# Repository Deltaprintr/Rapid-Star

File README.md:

# Overview

Rapid Star is a PNP (Pick and Place) system developed and maintained by [Deltaprintr](https://deltaprintr.com), run on the free [OpenPNP Software](https://openpnp.org) and [Mark's Smoothieware Firmware Version](https://makr.zone/smoothieware-new-firmware-for-pnp/500/) used for assembling circuit boards with the [Rapid Feeder](https://www.deltaprintr.com/product/rapid-feeder/) system. It features a conveyor belt that can hold boards up to 165mm (6.5") wide, 50 (8mm) feeders and has a head capable of supporting up to 8 nozzles with a 20 nozzle magazine auto-changer. Documentation on building a Rapid Star can be found [on our website](https://www.deltaprintr.com/docs/rapid-star/). The release is considered stable as the machine has been fully tested manually. If you would like to show your support for the project, consider purchasing [components directly from Deltaprintr](https://www.deltaprintr.com/product-category/smt-assembly/). This not only allows us to continue developing the Rapid Star, but also enables us to provide support directly to you in the process.

If you'd like to find out once Deltaprintr starts offering a complete kit, you can subscribe to our [mailing list](https://mailchi.mp/ee676e0cfc9f/rapidstar)

# Benefits of a star design
- Scalable nozzle count at no additional cost
- Higher CPH
- Simpler mechanical assembly
- More X/Y space due to smaller head, which means more space for feeders/trays.

# Contribute

Currently the Rapid Star is not fully supported in OpenPNP due to a few missing mandatory features. We're actively looking for developers who would be interested in helping us incorporate support into OpenPNP. You can see the [full list of features here](https://docs.google.com/document/d/1N6ggEopUlor0r7kC39QZDpr8pi3T8QCvNgg1l5aPtP0/edit?usp=sharing). If you're interested in helping, let us know on our [Discord Server](https://discord.gg/t2FcjAU7hC)!

If you'd like to keep up with the latest news you can also follow us on [Instagram](https://www.instagram.com/deltaprintr/), [Facebook](https://www.facebook.com/Deltaprintr/) or [Twitter](https://twitter.com/deltaprintr)!

# Support

While you are free to source and build a Rapid Star on your own, we are only able to provide support for customers who purchase components directly from us. This way we can guarantee your parts came from a reputable source and have a warranty. It's worth noting that some custom parts such as the head must be machined to a high tolerance to ensure air does not leak. For this reason, we recommend to get parts directly from us as it will save you time and frustration. However, if you do decide to source parts elsewhere, we do have a community of users who would be happy to help you on our [Discord Server](https://discord.gg/t2FcjAU7hC).

You can view a 3D model of the full assembly in your browser here: https://autode.sk/3zCK5wB

Support questions submitted via Github will be deleted. Only bugs/issues should be submitted via Github.

# Github Structure
- Mechanics (Full machine assembly)
- Electronics (Rapid Board, Conveyor, C Endstop, Nozzle Magazine, Feeder Extension, Feeder Motherboard)
- Firmware (Smoothieware and config)
- Openpnp Settings (OpenPNP machine.xml)
- Jigs (Lens calibration PCB)
- Scripts (Gcode for upward lens cam calibration)

# Programs Used
- Fusion 360
- Eagle CAD

# License

Rapid Star is licensed under [CC BY-NC-SA](https://creativecommons.org/licenses/by-nc-sa/4.0/): This license allows reusers to distribute, remix, adapt, and build upon the material in any medium or format for **non-commercial purposes only**, and only so long as attribution is given to the creator. If you remix, adapt, or build upon the material, you must license the modified material under identical terms. 

CC BY-NC-SA includes the following elements:

* BY  – Credit must be given to the creator
* NC  – Only non-commercial uses of the work are permitted
* SA  – Adaptations must be shared under the same terms

Deltaprintr, Rapid Star and Rapid Feeder are trademarks of Deltaprinter Inc. Other trademarks may be pending.

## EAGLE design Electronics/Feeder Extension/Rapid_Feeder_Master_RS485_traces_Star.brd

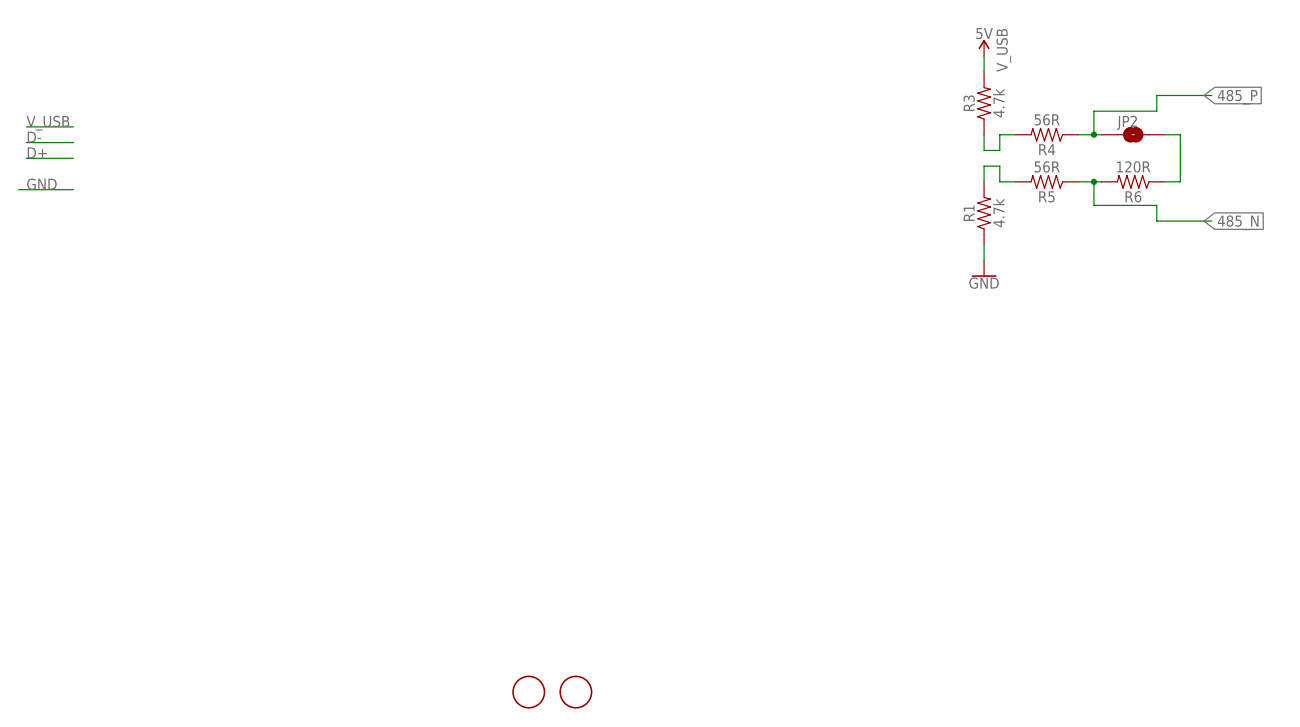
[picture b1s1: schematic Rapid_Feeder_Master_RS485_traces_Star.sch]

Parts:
JP2: JUMPER-SMT_2_NO_NO-SILK; SMT-JUMPER_2_NO_NO-SILK
R1, R3: 4.7k; R0603
R4, R5: 56R; R0603
R6: 120R; R0603
U$1, U$2: FIDUCIAL; FIDUCIAL_1MM

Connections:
485_N: R5.1, R6.2
485_P: JP2.1, R4.1
GND: R1.1
unnamed: R3.1, R4.2
unnamed: R1.2, R5.2
unnamed: JP2.2, R6.1
V_USB: R3.2

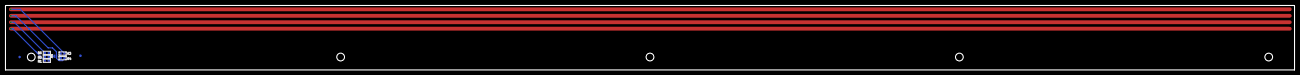
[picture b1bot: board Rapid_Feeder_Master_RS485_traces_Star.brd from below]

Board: 2 copper layers, 500.0 x 25.0 mm, 8 parts (8 on the bottom side), 5 nets.

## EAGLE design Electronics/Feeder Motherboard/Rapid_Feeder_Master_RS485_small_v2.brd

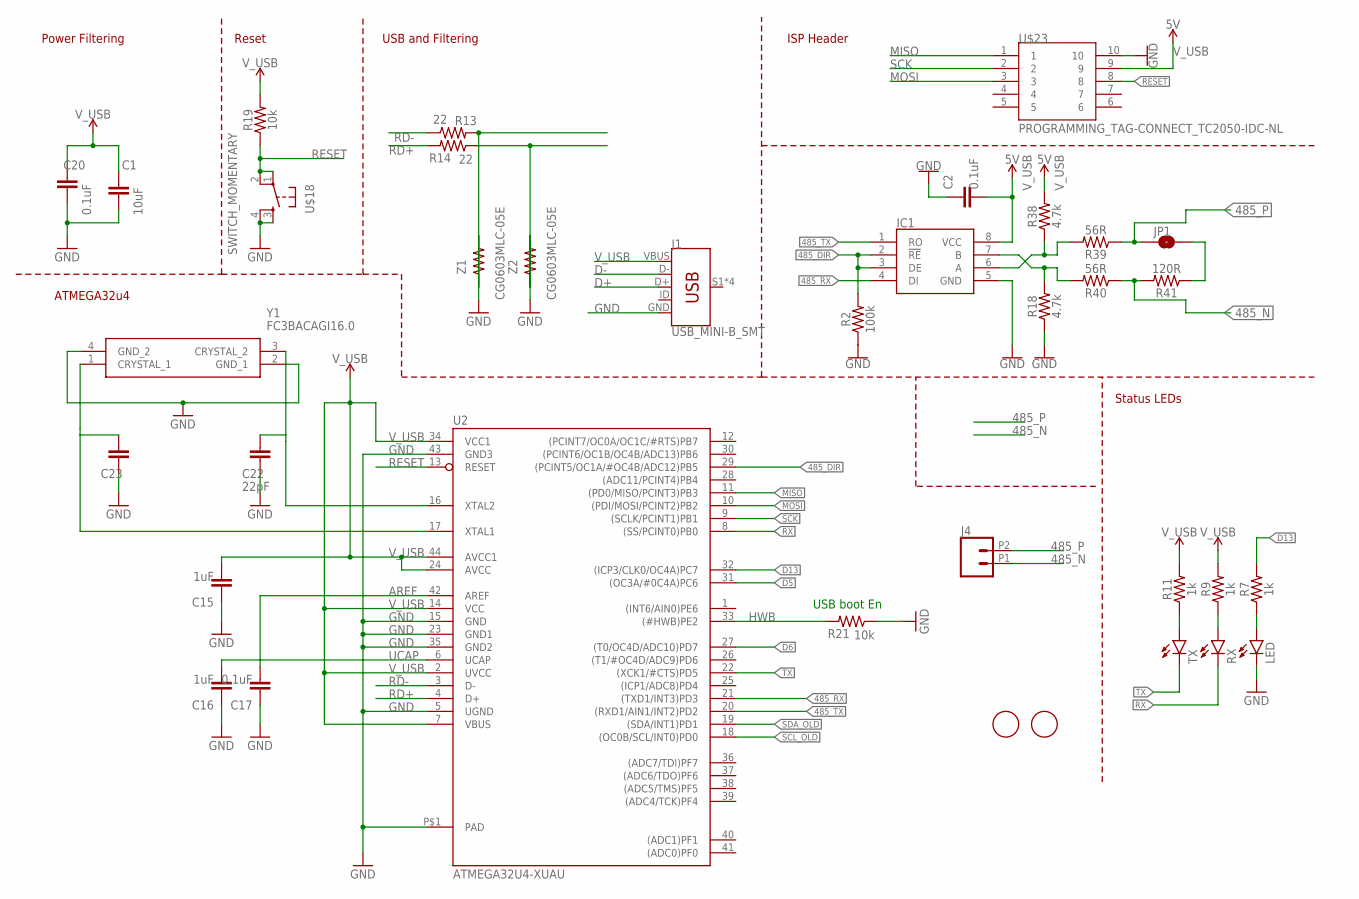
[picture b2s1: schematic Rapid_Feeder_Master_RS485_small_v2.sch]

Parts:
C1: 10uF; C0805
C2, C17, C20: 0.1uF; CAP_0603
C15, C16: 1uF; CAP_0603
C22, C23: 22pF; CAP_0603
IC1: ADM4850ARZ-REEL7; SOIC127P600X175-8N
J1: USB_MINI-B_SMT; USB-MINIB
J4: CONN_022.54MM_SCREWTERM; 1X02_2.54_SCREWTERM
JP1: JUMPER-SMT_2_NO_NO-SILK; SMT-JUMPER_2_NO_NO-SILK
LED: LED0603; LED-0603
R2: 100k; RESISTOR_0603
R7, R9, R11: 1k; RESISTOR_0603
R13, R14: 22; RESISTOR_0603
R18, R38: 4.7k; RESISTOR_0603
R19, R21: 10k; RESISTOR_0603
R39, R40: 56R; RESISTOR_0603
R41: 120R; RESISTOR_0603
RX: LED0603; LED-0603
TX: LED0603; LED-0603
U2: ATMEGA32U4-XUAU; TQFP44-PAD
U$1, U$2: FIDUCIAL; FIDUCIAL_1MM
U$18: SWITCH_MOMENTARY
U$23: PROGRAMMING_TAG-CONNECT_TC2050-IDC-NL
Y1: FC3BACAGI16.0; FC3BACAGI160
Z1, Z2: CG0603MLC-05E; RESISTOR_0603

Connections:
485_DIR: IC1.2 (!RE), IC1.3 (DE), R2.2, U2.29 ((PCINT5/OC1A/#OC4B/ADC12)PB5)
485_N: J4.P1 (1), R40.1, R41.2
485_P: J4.P2 (2), JP1.1, R39.1
485_RX: IC1.4 (DI), U2.21 ((TXD1/INT3)PD3)
485_TX: IC1.1 (RO), U2.20 ((RXD1/AIN1/INT2)PD2)
AREF: C17.2, U2.42 (AREF)
D5: U2.31 ((OC3A/#0C4A)PC6)
D6: U2.27 ((T0/OC4D/ADC10)PD7)
D13: R7.2, U2.32 ((ICP3/CLK0/OC4A)PC7)
D+: J1.D+, R14.1, Z2.1
D-: J1.D-, R13.2, Z1.1
GND: C1.1, C2.1, C15.1, C16.1, C17.1, C20.1, C22.2, C23.2, IC1.5 (GND), J1.GND, LED.C, R2.1, R18.1, R21.1, U2.5 (UGND), U2.15 (GND), U2.23 (GND1), U2.35 (GND2), U2.43 (GND3), U2.P$1 (PAD), U$18.3, U$18.4, U$23.10, Y1.2 (GND_1), Y1.4 (GND_2), Z1.2, Z2.2
HWB: R21.2, U2.33 ((#HWB)PE2)
MISO: U2.11 ((PD0/MISO/PCINT3)PB3), U$23.1
MOSI: U2.10 ((PDI/MOSI/PCINT2)PB2), U$23.3
unnamed: R11.1, TX.A
unnamed: IC1.6 (A), R38.1, R39.2
unnamed: IC1.7 (B), R18.2, R40.2
unnamed: JP1.2, R41.1
unnamed: R9.1, RX.A
unnamed: LED.A, R7.1
RD+: R14.2, U2.4 (D+)
RD-: R13.1, U2.3 (D-)
RESET: R19.1, U2.13 (RESET), U$18.1, U$18.2, U$23.8
RX: RX.C, U2.8 ((SS/PCINT0)PB0)
SCK: U2.9 ((SCLK/PCINT1)PB1), U$23.2
SCL_OLD: U2.18 ((OC0B/SCL/INT0)PD0)
SDA_OLD: U2.19 ((SDA/INT1)PD1)
TX: TX.C, U2.22 ((XCK1/#CTS)PD5)
UCAP: C16.2, U2.6 (UCAP)
V_USB: C1.2, C2.2, C15.2, C20.2, IC1.8 (VCC), J1.VBUS, R9.2, R11.2, R19.2, R38.2, U2.2 (UVCC), U2.7 (VBUS), U2.14 (VCC), U2.24 (AVCC), U2.34 (VCC1), U2.44 (AVCC1), U$23.9
XTAL3: C22.1, U2.16 (XTAL2), Y1.3 (CRYSTAL_2)
XTAL4: C23.1, U2.17 (XTAL1), Y1.1 (CRYSTAL_1)

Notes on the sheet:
USB boot En
Power Filtering
Reset
USB and Filtering
ISP Header
ATMEGA32u4
Status LEDs

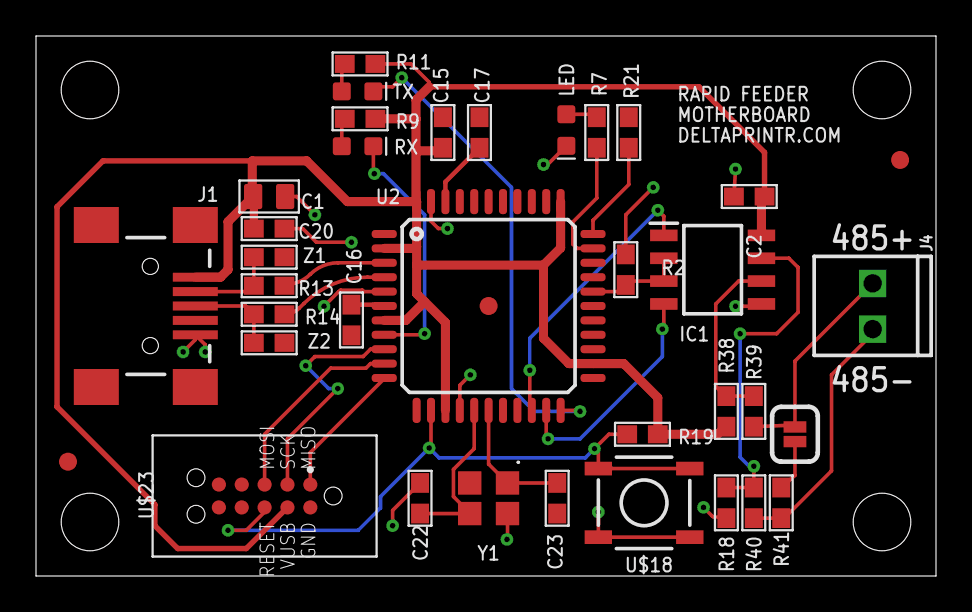
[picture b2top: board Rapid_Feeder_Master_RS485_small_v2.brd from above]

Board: 2 copper layers, 50.0 x 30.0 mm, 36 parts (0 on the bottom side), 29 nets.

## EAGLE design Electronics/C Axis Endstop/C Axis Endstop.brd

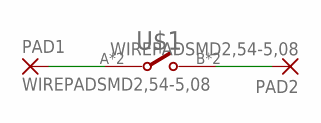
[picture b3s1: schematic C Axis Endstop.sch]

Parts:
PAD1, PAD2: WIREPADSMD2,54-5,08; SMD2,54-5,08
U$1: SWITCH_LIMIT_HDP001L

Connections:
unnamed: PAD1.1, U$1.A (1), U$1.C (1)
unnamed: PAD2.1, U$1.B (2), U$1.D (2)

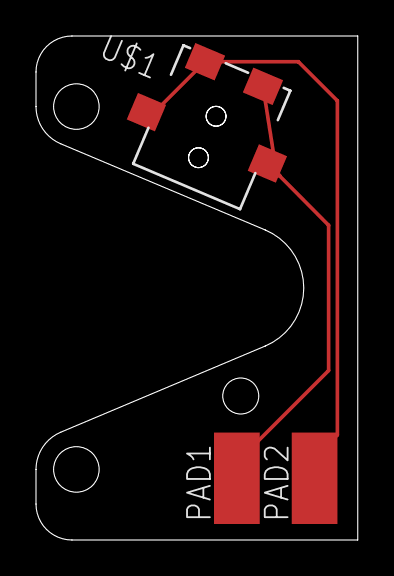
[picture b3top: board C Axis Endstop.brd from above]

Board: 2 copper layers, 17.9 x 28.0 mm, 3 parts (0 on the bottom side), 2 nets.

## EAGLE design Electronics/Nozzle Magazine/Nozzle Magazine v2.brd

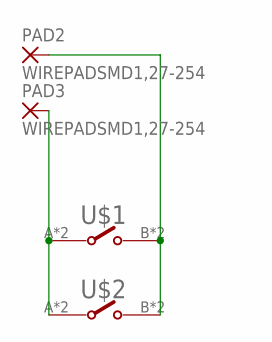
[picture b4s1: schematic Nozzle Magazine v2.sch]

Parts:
PAD2, PAD3: WIREPADSMD1,27-254; SMD1,27-2,54
U$1, U$2: SWITCH_LIMIT_HDP001L

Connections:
unnamed: PAD3.1, U$1.A (1), U$1.C (1), U$2.A (1), U$2.C (1)
unnamed: PAD2.1, U$1.B (2), U$1.D (2), U$2.B (2), U$2.D (2)

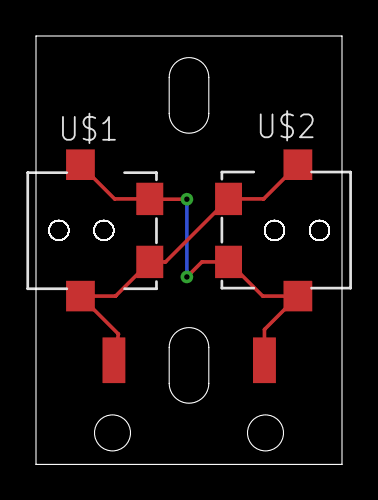
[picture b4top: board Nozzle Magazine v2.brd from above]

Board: 2 copper layers, 17.0 x 23.8 mm, 4 parts (0 on the bottom side), 2 nets.

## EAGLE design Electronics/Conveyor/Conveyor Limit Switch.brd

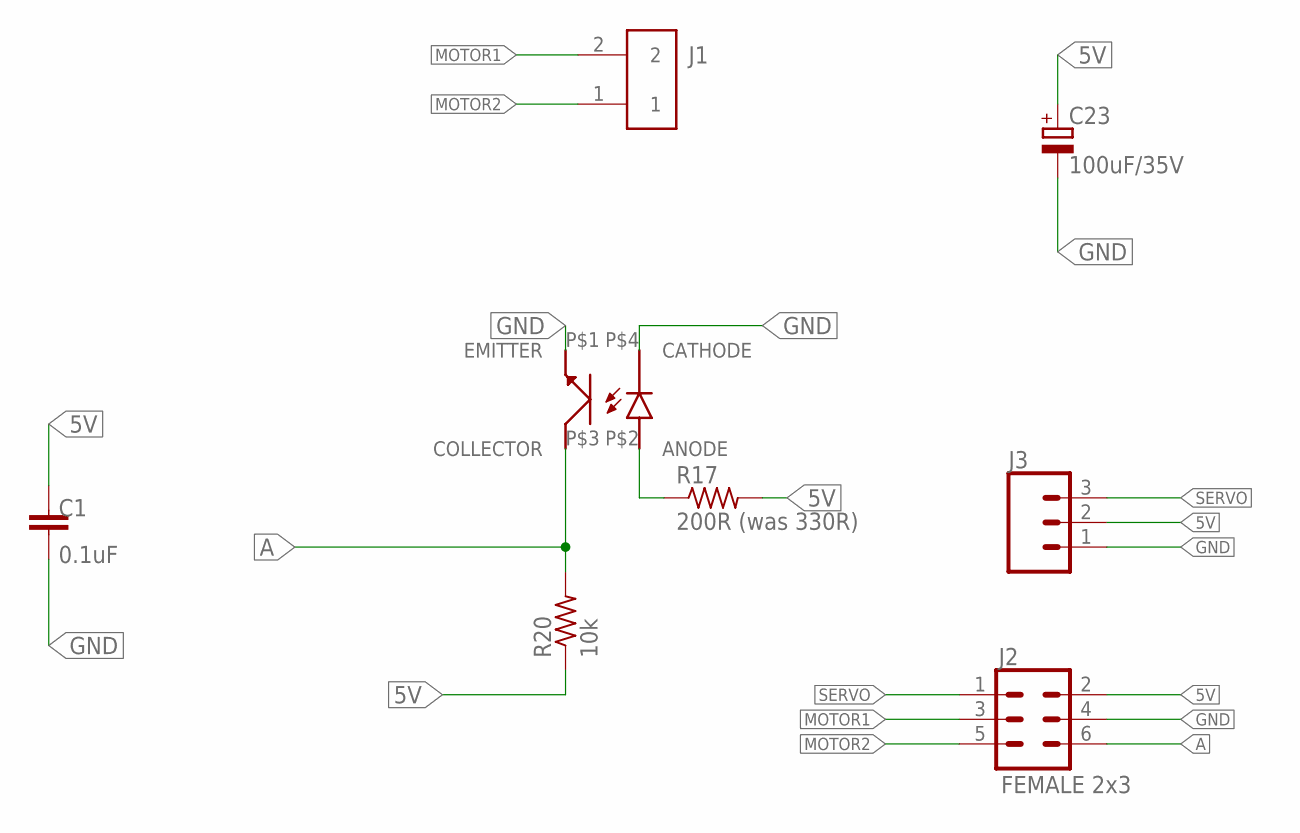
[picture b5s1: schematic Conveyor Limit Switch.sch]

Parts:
C1: 0.1uF; CAP_0603
C23: 100uF/35V; 153CLV-0605
J1: S2B-PH-SM4-TB(LF)(SN); S2B-PH-SM4-TB
J2: FEMALE 2x3; 2X3
J3: CONN_03; 1X03
R17: 200R (was 330R); RESISTOR_0603
R20: 10k; RESISTOR_0603
U$2: IR_VCNT2020

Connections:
5V: C1.1, C23.+, J2.2, J3.2, R17.2, R20.1
A: J2.6, R20.2, U$2.P$3 (COLLECTOR)
GND: C1.2, C23.-, J2.4, J3.1, U$2.P$1 (EMITTER), U$2.P$4 (CATHODE)
LED2: R17.1, U$2.P$2 (ANODE)
MOTOR1: J1.2, J2.3
MOTOR2: J1.1, J2.5
SERVO: J2.1, J3.3

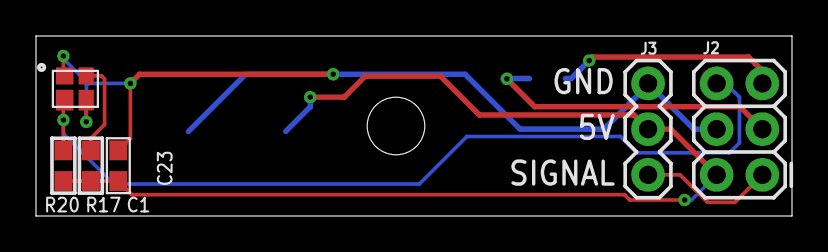
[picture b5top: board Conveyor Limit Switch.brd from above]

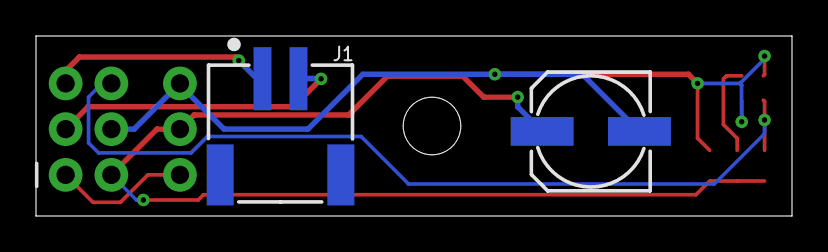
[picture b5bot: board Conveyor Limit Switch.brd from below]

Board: 2 copper layers, 42.0 x 10.0 mm, 8 parts (2 on the bottom side), 7 nets.

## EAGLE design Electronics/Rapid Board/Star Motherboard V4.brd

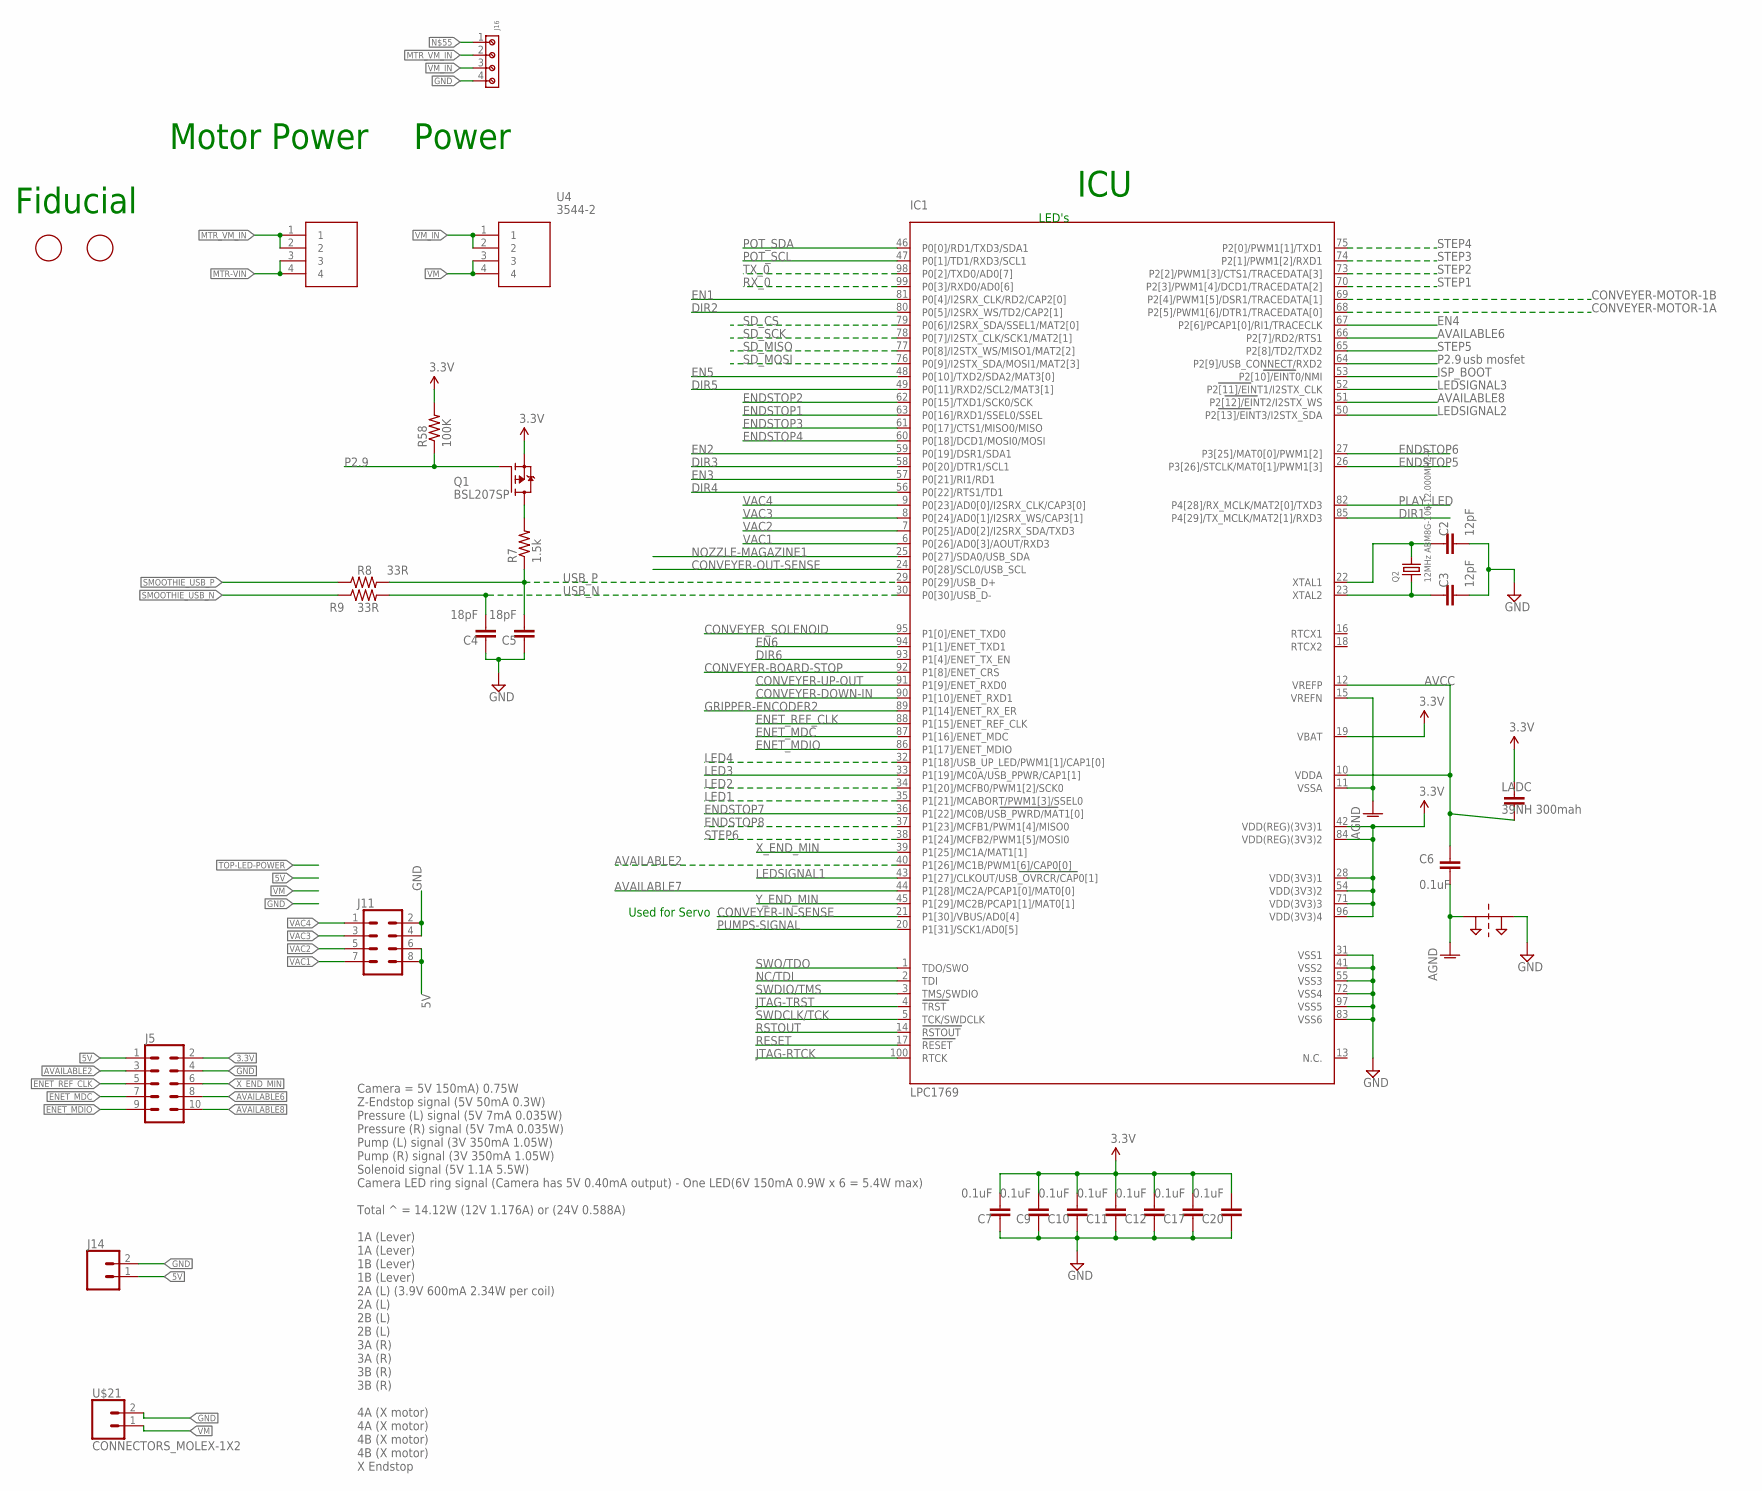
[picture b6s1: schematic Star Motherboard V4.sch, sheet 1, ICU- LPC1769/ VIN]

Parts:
C2, C3: 12pF; CAP_0603
C4, C5: 18pF; CAP_0603
C6, C7, C9, C10, C11, C12, C17, C20: 0.1uF; CAP_0603
IC1: LPC1769
J5: CONN_05X2PTH; 2X5
J11: CONN_04X2; 2X4
J14: CONN_02; 1X02
J16: 691137710004
LADC: 39NH 300mah; CAP_0603
Q1: BSL207SP; SC74_INFINEON
Q2: 12MHz ABM8G-106-12.000MHZ-T; CRYSTAL_3.2X2.5
R7: 1.5k; RESISTOR_0603
R8, R9: 33R; RESISTOR_0603
R58: 100K; RESISTOR_0603
SUPPLY10: 2PT_GND_TIE
U1, U4: 3544-2
U$9, U$10: FIDUCIAL; FIDUCIAL_1MM
U$21: CONNECTORS_MOLEX-1X2

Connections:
3.3V: C7.2, C9.2, C10.2, C11.2, C12.2, C17.2, C20.2, IC1.19 (VBAT), IC1.28 (VDD(3V3)1), IC1.42 (VDD(REG)(3V3)1), IC1.54 (VDD(3V3)2), IC1.71 (VDD(3V3)3), IC1.84 (VDD(REG)(3V3)2), IC1.96 (VDD(3V3)4), J5.2, LADC.1, Q1.4 (S), R58.2; also elsewhere on the board
5V: J5.1, J11.6, J11.8, J14.1; also elsewhere on the board
AGND: C6.2, IC1.11 (VSSA), IC1.15 (VREFN), SUPPLY10.P$1; also elsewhere on the board
AVAILABLE2: IC1.40 (P1[26]/MC1B/PWM1[6]/CAP0[0]), J5.3
AVAILABLE6: IC1.66 (P2[7]/RD2/RTS1), J5.8
AVAILABLE7: IC1.44 (P1[28]/MC2A/PCAP1[0]/MAT0[0]); also elsewhere on the board
AVAILABLE8: IC1.51 (P2[12]/EINT2/I2STX_WS), J5.10
AVCC: C6.1, IC1.10 (VDDA), IC1.12 (VREFP), LADC.2; also elsewhere on the board
CONVEYER-BOARD-STOP: IC1.92 (P1[8]/ENET_CRS); also elsewhere on the board
CONVEYER-DOWN-IN: IC1.90 (P1[10]/ENET_RXD1); also elsewhere on the board
CONVEYER-IN-SENSE: IC1.21 (P1[30]/VBUS/AD0[4]); also elsewhere on the board
CONVEYER-MOTOR-1A: IC1.68 (P2[5]/PWM1[6]/DTR1/TRACEDATA[0]); also elsewhere on the board
CONVEYER-MOTOR-1B: IC1.69 (P2[4]/PWM1[5]/DSR1/TRACEDATA[1]); also elsewhere on the board
CONVEYER-OUT-SENSE: IC1.24 (P0[28]/SCL0/USB_SCL); also elsewhere on the board
CONVEYER-UP-OUT: IC1.91 (P1[9]/ENET_RXD0); also elsewhere on the board
CONVEYER_SOLENOID: IC1.95 (P1[0]/ENET_TXD0); also elsewhere on the board
DIR1: IC1.85 (P4[29]/TX_MCLK/MAT2[1]/RXD3); also elsewhere on the board
DIR2: IC1.80 (P0[5]/I2SRX_WS/TD2/CAP2[1]); also elsewhere on the board
DIR3: IC1.58 (P0[20]/DTR1/SCL1); also elsewhere on the board
DIR4: IC1.56 (P0[22]/RTS1/TD1); also elsewhere on the board
DIR5: IC1.49 (P0[11]/RXD2/SCL2/MAT3[1]); also elsewhere on the board
DIR6: IC1.93 (P1[4]/ENET_TX_EN); also elsewhere on the board
EN1: IC1.81 (P0[4]/I2SRX_CLK/RD2/CAP2[0]); also elsewhere on the board
EN2: IC1.59 (P0[19]/DSR1/SDA1); also elsewhere on the board
EN3: IC1.57 (P0[21]/RI1/RD1); also elsewhere on the board
EN4: IC1.67 (P2[6]/PCAP1[0]/RI1/TRACECLK); also elsewhere on the board
EN5: IC1.48 (P0[10]/TXD2/SDA2/MAT3[0]); also elsewhere on the board
EN6: IC1.94 (P1[1]/ENET_TXD1); also elsewhere on the board
ENDSTOP1: IC1.63 (P0[16]/RXD1/SSEL0/SSEL); also elsewhere on the board
ENDSTOP2: IC1.62 (P0[15]/TXD1/SCK0/SCK); also elsewhere on the board
ENDSTOP3: IC1.61 (P0[17]/CTS1/MISO0/MISO); also elsewhere on the board
ENDSTOP4: IC1.60 (P0[18]/DCD1/MOSI0/MOSI); also elsewhere on the board
ENDSTOP5: IC1.26 (P3[26]/STCLK/MAT0[1]/PWM1[3]); also elsewhere on the board
ENDSTOP6: IC1.27 (P3[25]/MAT0[0]/PWM1[2]); also elsewhere on the board
ENDSTOP7: IC1.36 (P1[22]/MC0B/USB_PWRD/MAT1[0]); also elsewhere on the board
ENDSTOP8: IC1.37 (P1[23]/MCFB1/PWM1[4]/MISO0); also elsewhere on the board
ENET_MDC: IC1.87 (P1[16]/ENET_MDC), J5.7
ENET_MDIO: IC1.86 (P1[17]/ENET_MDIO), J5.9
ENET_REF_CLK: IC1.88 (P1[15]/ENET_REF_CLK), J5.5
GND: C2.2, C3.2, C4.1, C5.1, C7.1, C9.1, C10.1, C11.1, C12.1, C17.1, C20.1, IC1.31 (VSS1), IC1.41 (VSS2), IC1.55 (VSS3), IC1.72 (VSS4), IC1.83 (VSS6), IC1.97 (VSS5), J5.4, J11.2, J11.4, J14.2, J16.4, SUPPLY10.P$2, U$21.2; also elsewhere on the board
GRIPPER-ENCODER2: IC1.89 (P1[14]/ENET_RX_ER); also elsewhere on the board
ISP_BOOT: IC1.53 (P2[10]/EINT0/NMI); also elsewhere on the board
JTAG-RTCK: IC1.100 (RTCK)
JTAG-TRST: IC1.4 (TRST)
LED1: IC1.35 (P1[21]/MCABORT/PWM1[3]/SSEL0); also elsewhere on the board
LED2: IC1.34 (P1[20]/MCFB0/PWM1[2]/SCK0); also elsewhere on the board
LED3: IC1.33 (P1[19]/MC0A/USB_PPWR/CAP1[1]); also elsewhere on the board
LED4: IC1.32 (P1[18]/USB_UP_LED/PWM1[1]/CAP1[0]); also elsewhere on the board
LEDSIGNAL1: IC1.43 (P1[27]/CLKOUT/USB_OVRCR/CAP0[1]); also elsewhere on the board
LEDSIGNAL2: IC1.50 (P2[13]/EINT3/I2STX_SDA); also elsewhere on the board
LEDSIGNAL3: IC1.52 (P2[11]/EINT1/I2STX_CLK); also elsewhere on the board
MTR-VIN: U1.3, U1.4; also elsewhere on the board
MTR_VM_IN: J16.2, U1.1, U1.2
unnamed: C2.1, IC1.22 (XTAL1), Q2.2
unnamed: C3.1, IC1.23 (XTAL2), Q2.1
unnamed: Q1.1 (D), Q1.2 (D), Q1.5 (D), Q1.6 (D), R7.2
NC/TDI: IC1.2 (TDI)
NOZZLE-MAGAZINE1: IC1.25 (P0[27]/SDA0/USB_SDA); also elsewhere on the board
P2.9: IC1.64 (P2[9]/USB_CONNECT/RXD2), Q1.3 (G), R58.1
PLAY_LED: IC1.82 (P4[28]/RX_MCLK/MAT2[0]/TXD3); also elsewhere on the board
POT_SCL: IC1.47 (P0[1]/TD1/RXD3/SCL1); also elsewhere on the board
POT_SDA: IC1.46 (P0[0]/RD1/TXD3/SDA1); also elsewhere on the board
PUMPS-SIGNAL: IC1.20 (P1[31]/SCK1/AD0[5]); also elsewhere on the board
RESET: IC1.17 (RESET); also elsewhere on the board
RSTOUT: IC1.14 (RSTOUT)
RX_0: IC1.99 (P0[3]/RXD0/AD0[6]); also elsewhere on the board
SD_CS: IC1.79 (P0[6]/I2SRX_SDA/SSEL1/MAT2[0]); also elsewhere on the board
SD_MISO: IC1.77 (P0[8]/I2STX_WS/MISO1/MAT2[2]); also elsewhere on the board
SD_MOSI: IC1.76 (P0[9]/I2STX_SDA/MOSI1/MAT2[3]); also elsewhere on the board
SD_SCK: IC1.78 (P0[7]/I2STX_CLK/SCK1/MAT2[1]); also elsewhere on the board
SMOOTHIE_USB_N: R9.1; also elsewhere on the board
SMOOTHIE_USB_P: R8.1; also elsewhere on the board
STEP1: IC1.70 (P2[3]/PWM1[4]/DCD1/TRACEDATA[2]); also elsewhere on the board
STEP2: IC1.73 (P2[2]/PWM1[3]/CTS1/TRACEDATA[3]); also elsewhere on the board
STEP3: IC1.74 (P2[1]/PWM1[2]/RXD1); also elsewhere on the board
STEP4: IC1.75 (P2[0]/PWM1[1]/TXD1); also elsewhere on the board
STEP5: IC1.65 (P2[8]/TD2/TXD2); also elsewhere on the board
STEP6: IC1.38 (P1[24]/MCFB2/PWM1[5]/MOSI0); also elsewhere on the board
SWDCLK/TCK: IC1.5 (TCK/SWDCLK)
SWDIO/TMS: IC1.3 (TMS/SWDIO)
SWO/TDO: IC1.1 (TDO/SWO)
TX_0: IC1.98 (P0[2]/TXD0/AD0[7]); also elsewhere on the board
USB_N: C4.2, IC1.30 (P0[30]/USB_D-), R9.2
USB_P: C5.2, IC1.29 (P0[29]/USB_D+), R7.1, R8.2
VAC1: IC1.6 (P0[26]/AD0[3]/AOUT/RXD3), J11.7; also elsewhere on the board
VAC2: IC1.7 (P0[25]/AD0[2]/I2SRX_SDA/TXD3), J11.5; also elsewhere on the board
VAC3: IC1.8 (P0[24]/AD0[1]/I2SRX_WS/CAP3[1]), J11.3; also elsewhere on the board
VAC4: IC1.9 (P0[23]/AD0[0]/I2SRX_CLK/CAP3[0]), J11.1; also elsewhere on the board
VM: U4.3, U4.4, U$21.1; also elsewhere on the board
VM_IN: J16.3, U4.1, U4.2
X_END_MIN: IC1.39 (P1[25]/MC1A/MAT1[1]), J5.6
Y_END_MIN: IC1.45 (P1[29]/MC2B/PCAP1[1]/MAT0[1]); also elsewhere on the board

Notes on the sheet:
usb mosfet
LED's
ICU
Fiducial
Power
Camera = 5V 150mA) 0.75W Z-Endstop signal (5V 50mA 0.3W) Pressure (L) signal (5V 7mA 0.035W) Pressure (R) signal (5V 7mA 0.035W) Pump (L) signal (3V 350mA 1.05W) Pump (R) signal (3V 350mA 1.05W) Solenoid signal (5V 1.1A 5.5W) Camera LED ring signal (Camera has 5V 0.40mA output) - One LED(6V 150mA 0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
Used for Servo
Motor Power

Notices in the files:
parts and their libraries:
SparkFun-Connectors: Licensing: Creative Commons ShareAlike 4.0 International - https://creativecommons.org/licenses/by-sa/4.0
Inductors-Griff: Copyright (C) 2007, Bob Starr
Wurth_Connectors_WR-TBL Wire Protector: Copyright: Würth Elektronik
